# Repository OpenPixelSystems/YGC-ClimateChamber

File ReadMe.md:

# Climate Chamber Control System - Technical Documentation

A Flask-based climate chamber control system for Raspberry Pi providing precise temperature control using Peltier elements, real-time monitoring, and flow-based control sequences.

## Overview

This technical documentation is intended for developers and system administrators who need to understand the architecture, modify the system, or add new hardware components.

**For Users**: See `USER_GUIDE.md` for connection instructions and `INTERFACE_MANUAL.md` for application usage.

**Key Technologies:**
- Flask 3.1.1 web framework with Jinja2 templates
- RPi.GPIO for hardware control
- Adafruit CircuitPython libraries for sensors
- SQLite for data logging
- Chart.js for real-time visualization
- PID-based temperature control

---

## Architecture

### Frontend

The frontend is a Flask-rendered web application using HTML templates, JavaScript, and CSS.

**Location:** `app/frontend/`

**Technologies:**
- **Flask Templates (Jinja2)**: Server-side HTML rendering
- **JavaScript**: Client-side interactivity and real-time updates
- **CSS**: Custom styling with responsive design
- **AJAX**: Asynchronous communication with backend APIs

**Key Pages:**
- `home.html` - Main dashboard with quick temperature input
- `setupGraph.html` - Temperature profile creation interface
- `displayGraph.html` - Real-time graph display during active cycles
- `manualControl.html` - Manual hardware control interface
- `flow_designer.html` - Visual flow-based control designer
- `configEditor.html` - System configuration editor
- `databaseViewer.html` - Historical data viewer
- `logs_viewer.html` - System logs browser
- `wifi_networks.html` - WiFi network configuration

**Frontend Features:**
- Real-time temperature plotting using Chart.js or similar
- Drag-and-drop flow designer for creating temperature sequences
- Responsive forms for configuration editing
- Live status updates via periodic AJAX polling
- Flash messages for user feedback

---

### Backend

The backend follows a modular, interface-driven architecture with clear separation of concerns.

**Location:** `app/backend/`

**Technologies:**
- **Flask 3.1.1**: Web framework and API routing
- **RPi.GPIO**: Raspberry Pi GPIO control for hardware interfacing
- **Adafruit CircuitPython Libraries**:
  - `adafruit-circuitpython-mpl3115a2` - Pressure/temperature sensor
  - `adafruit-circuitpython-ads1x15` - Analog-to-Digital converter
- **SQLite**: Local database for data logging (`database.db`)
- **Python 3.x**: Core programming language

**Architecture Layers:**

#### 1. **Interfaces** (`app/backend/Interfaces/`)
Define contracts for all major components:
- `ISensor.py` - Sensor reading interface
- `IDriver.py` - Hardware driver interface
- `IClimateChamber.py` - Climate control interface
- `IConfigManager.py` - Configuration management
- `IDatabaseManager.py` - Database operations
- And more...

#### 2. **Implementations** (`app/backend/Implementations/`)
Concrete implementations of interfaces:
- `ClimateChamber.py` - Main climate control logic with PID control
- `ClimateChamberController.py` - High-level controller orchestration
- `SensorReader.py` - Reads all configured sensors
- `ConfigManager.py` - Loads and validates JSON configurations
- `DatabaseManager.py` - SQLite operations for logging and retrieval
- `FanController.py` - Fan speed control
- `RelayController.py` - Relay switching (e.g., for fridge control)

#### 3. **Drivers** (`app/backend/Drivers/`)
Low-level hardware drivers for motor controllers:
- `BTS7960Driver.py` - High-power motor driver for Peltier modules (up to 43A)
- `TB6612FNGDriver.py` - Dual motor driver for smaller Peltier/fan modules

#### 4. **Sensors** (`app/backend/Sensors/`)
Sensor implementations:
- `NTCTemperatureSensor.py` - NTC thermistor reading via ADC
- `DS18B20.py` - Digital temperature sensor (1-Wire)
- `DS18B20Cluster.py` - Multiple DS18B20 sensors
- `MPL3115A2.py` - I2C pressure and temperature sensor
- `ADS1115.py` - 16-bit ADC for analog sensors

#### 5. **Modules** (`app/backend/Modules/`)
Higher-level hardware abstractions:
- `PeltierModule.py` - Peltier element control (heating/cooling)
- `FanModule.py` - Fan control with PWM speed adjustment

#### 6. **Services** (`app/backend/Services/`)
Business logic and orchestration:
- `GuardingService.py` - Safety monitoring and emergency stops
- `TemperatuurService.py` - Temperature validation and processing
- `CalculationService.py` - PID calculations and control algorithms

#### 7. **Configuration** (`app/backend/config/`)
JSON-based configuration files:
- `raspberry_pi_config.json` - Hardware pin mappings and sensor definitions
- `control_config.json` - PID parameters and control settings
- `graph_config.json` - Stored temperature profiles

#### 8. **Flow Execution** (`app/backend/FlowExecution/`)
- `FlowExecutor.py` - Executes visual flow-based temperature sequences

#### 9. **Application State** (`app/backend/app_state.py`)
Singleton pattern for managing global application state:
- Initializes all components via factory methods
- Provides shared access to services and controllers
- Handles system reload and restart operations

---

## How It Works

### 1. **Temperature Control Loop**

The system uses a PID (Proportional-Integral-Derivative) control loop:

1. **Sensor Reading**: `SensorReader` polls all configured temperature sensors
2. **Calculation**: `CalculationService` compares current vs. desired temperature and calculates PID output
3. **Hardware Control**: Based on PID output:
   - **Positive output** → Heat mode: Peltier modules heat, fridge relay OFF
   - **Negative output** → Cool mode: Peltier modules cool or fridge relay ON
4. **Safety Monitoring**: `GuardingService` continuously checks sensor limits
5. **Logging**: `DatabaseManager` records all data points to SQLite database

### 2. **Peltier Module Control**

Peltier elements are thermoelectric devices that can heat or cool based on current direction:

- **Heating**: Current flows one direction (RPWM active, LPWM off)
- **Cooling**: Current flows opposite direction (LPWM active, RPWM off)
- **PWM Duty Cycle**: Controls heating/cooling intensity (0-100%)
- **Driver Selection**: System supports BTS7960 (high power) or TB6612FNG (lower power)

### 3. **Web Interface Communication**

1. User creates temperature profile via web interface
2. Frontend sends AJAX request to Flask route
3. Route handler validates input and calls backend service
4. Backend starts control loop and begins logging
5. Frontend polls for updates and renders real-time graphs

### 4. **Configuration System**

All hardware is defined in `raspberry_pi_config.json`:
```json
{
  "Temperature_inside_top": {
    "type": "NTC",
    "editable": {
      "SDA": 2,
      "SCL": 3,
      "read_pin": 0,
      "i2c_address": "0x4A",
      "beta_coefficient": 3600.0
    }
  },
  "Peltier_240W": {
    "type": "peltier",
    "editable": {
      "driver_type": "BTS7960",
      "RPWM": 13,
      "LPWM": 19,
      "R_EN": 5,
      "L_EN": 6,
      "PWM_FREQUENCY": 5000,
      "Duty cycle limit": 100
    }
  }
}
```

---

## Hardware Configuration

### Supported Hardware Components

#### **Temperature Sensors**
- **NTC Thermistors**: Via ADS1115 16-bit ADC
- **DS18B20**: Digital 1-Wire temperature sensors
- **MPL3115A2**: I2C pressure and temperature sensor

#### **Peltier Drivers**
- **BTS7960**: High-current (up to 43A) dual H-bridge for large Peltier modules
- **TB6612FNG**: Dual DC motor driver for smaller modules

#### **Other Components**
- **Fans**: PWM-controlled cooling fans
- **Relays**: For controlling external devices (e.g., refrigerator)

---

## Adapting to Different Hardware

### Adding a New Sensor

1. **Create sensor class** in `app/backend/Sensors/`:
```python
from app.backend.Interfaces.ISensor import ISensor

class MySensor(ISensor):
    def __init__(self, config):
        self.config = config

    def read(self):
        # Your sensor reading logic
        return temperature_value
```

2. **Add to SensorReader** in `app/backend/Implementations/SensorReader.py`:
```python
elif sensor_config.type == "MySensor":
    from app.backend.Sensors.MySensor import MySensor
    sensor = MySensor(sensor_config)
```

3. **Update configuration** in `raspberry_pi_config.json`:
```json
{
  "My_Temperature_Sensor": {
    "name": "My_Temperature_Sensor",
    "type": "MySensor",
    "editable": {
      "gpio_pin": 17,
      "custom_parameter": 123
    },
    "unit": "degrees"
  }
}
```

### Adding a New Motor Driver

1. **Create driver class** in `app/backend/Drivers/`:
```python
from app.backend.Interfaces.IDriver import IDriver

class MyDriver(IDriver):
    def __init__(self, config):
        # Initialize GPIO pins
        pass

    def heat(self, duty_cycle):
        # Implement heating logic
        pass

    def cool(self, duty_cycle):
        # Implement cooling logic
        pass

    def stop(self):
        # Stop all outputs
        pass
```

2. **Add to PeltierModule** in `app/backend/Modules/PeltierModule.py`:
```python
class DriverType(Enum):
    TB6612FNG = "TB6612FNG"
    BTS7960 = "BTS7960"
    MY_DRIVER = "MY_DRIVER"  # Add your driver

# In __init__:
if self.driver_type == DriverType.MY_DRIVER.value:
    from app.backend.Drivers.MyDriver import MyDriver
    self.driver = MyDriver(config)
```

3. **Update configuration**:
```json
{
  "Peltier_Custom": {
    "type": "peltier",
    "editable": {
      "driver_type": "MY_DRIVER",
      "pin1": 13,
      "pin2": 19,
      "pwm_frequency": 5000
    }
  }
}
```

### Changing GPIO Pin Assignments

Edit `app/backend/config/raspberry_pi_config.json` to change pin numbers:
```json
{
  "Peltier_240W": {
    "editable": {
      "RPWM": 13,  // Change to your pin number
      "LPWM": 19,  // Change to your pin number
      "R_EN": 5,
      "L_EN": 6
    }
  }
}
```

**Important**: After changing GPIO pins, restart the service:
```bash
sudo systemctl restart climatechamber.service
```

---

## Development Setup

### Local Development

1. Clone repository and create virtual environment:
```bash
git clone https://gitlab.com/tmc-climatechamber/climatechamber.git
cd climatechamber
python -m venv .venv
source .venv/bin/activate  # On Windows: .venv\Scripts\activate
pip install -r requirements.txt
```

2. Run development server:
```bash
python run.py
```

3. Access at `http://localhost:5000`

### Raspberry Pi Deployment

The system is pre-configured to run as a systemd service on Raspberry Pi. For fresh installations:

1. Clone repository on Raspberry Pi
2. Run setup script: `./setup_rp4.sh`
3. Service starts automatically on boot

---

## Project Structure

```
climatechamber/
├── app/
│   ├── __init__.py                 # Flask app factory
│   ├── backend/
│   │   ├── app_state.py            # Singleton application state
│   │   ├── Dataclasses/            # Data models and configurations
│   │   ├── Drivers/                # Low-level hardware drivers
│   │   ├── Sensors/                # Sensor implementations
│   │   ├── Modules/                # Hardware module abstractions
│   │   ├── Implementations/        # Core business logic
│   │   ├── Interfaces/             # Abstract interfaces
│   │   ├── Services/               # Business services
│   │   ├── FlowExecution/          # Flow-based control
│   │   ├── Providers/              # GPIO and hardware providers
│   │   ├── Technical/              # Logging and utilities
│   │   └── config/                 # JSON configuration files
│   ├── frontend/
│   │   ├── static/                 # CSS, JS, fonts
│   │   └── templates/              # HTML templates
│   └── routes/                     # Flask route handlers
├── run.py                          # Application entry point
├── requirements.txt                # Python dependencies
├── database.db                     # SQLite database
├── setup_rp4.sh                    # Raspberry Pi setup script
└── README.md                       # This file
```

---

## API Routes

| Route | Method | Description |
|-------|--------|-------------|
| `/` | GET | Home page with quick temperature input |
| `/status` | GET | Health check endpoint |
| `/submit-temperature` | POST | Start constant temperature cycle |
| `/manual-control` | GET | Manual hardware control interface |
| `/setup-graph` | GET/POST | Create temperature profiles |
| `/display-graph` | GET | Real-time monitoring |
| `/flow-designer` | GET/POST | Visual flow designer |
| `/database-viewer` | GET | View historical data |
| `/config-editor` | GET/POST | Edit system configuration |
| `/logs` | GET | View system logs |
| `/wifi` | GET/POST | Manage WiFi connections |

---

## Configuration Files

### raspberry_pi_config.json
Defines all hardware components and GPIO pin mappings.

### control_config.json
Contains PID tuning parameters and control loop settings.

### graph_config.json
Stores saved temperature profiles.

---

## Safety Features

1. **Temperature Limits**: Configurable min/max values per sensor
2. **Safety-Critical Sensors**: Emergency stops if limits exceeded
3. **Guarding Service**: Continuous monitoring of all sensors
4. **Emergency Stop**: Immediate hardware shutdown capability
5. **Duty Cycle Limits**: Prevents over-driving Peltier elements
6. **Cycle Locking**: Prevents starting multiple cycles simultaneously

---

## Development

### Adding New Features

The system follows the **Interface-Implementation pattern**:
1. Define interface in `Interfaces/`
2. Create implementation in `Implementations/`
3. Register in `app_state.py` factory methods
4. Add route handler in `routes/`
5. Create frontend template if needed

### Testing

Unit tests are located in `unittest/` directory.

---

## Common Development Issues

### GPIO Permission Errors
```bash
sudo usermod -a -G gpio $USER
# Log out and back in for changes to take effect
```

### I2C Not Enabled
```bash
sudo raspi-config
# Interface Options → I2C → Enable
```

### Service Debugging
```bash
# View real-time logs
sudo journalctl -u climatechamber.service -f

# Check service status
sudo systemctl status climatechamber.service

# Restart service
sudo systemctl restart climatechamber.service
```

### Python Import Errors
Ensure virtual environment is activated and all dependencies are installed:
```bash
source .venv/bin/activate
pip install -r requirements.txt
```

---

## Contributing

When adding new features:
1. Follow the Interface-Implementation pattern
2. Add corresponding route handlers in `app/routes/`
3. Update frontend templates as needed
4. Document changes in code comments
5. Test thoroughly before committing

---

## License

[Add your license information here]

## Support

For technical issues, check the logs and review this documentation. For user-facing questions, direct users to `USER_GUIDE.md` and `INTERFACE_MANUAL.md`.

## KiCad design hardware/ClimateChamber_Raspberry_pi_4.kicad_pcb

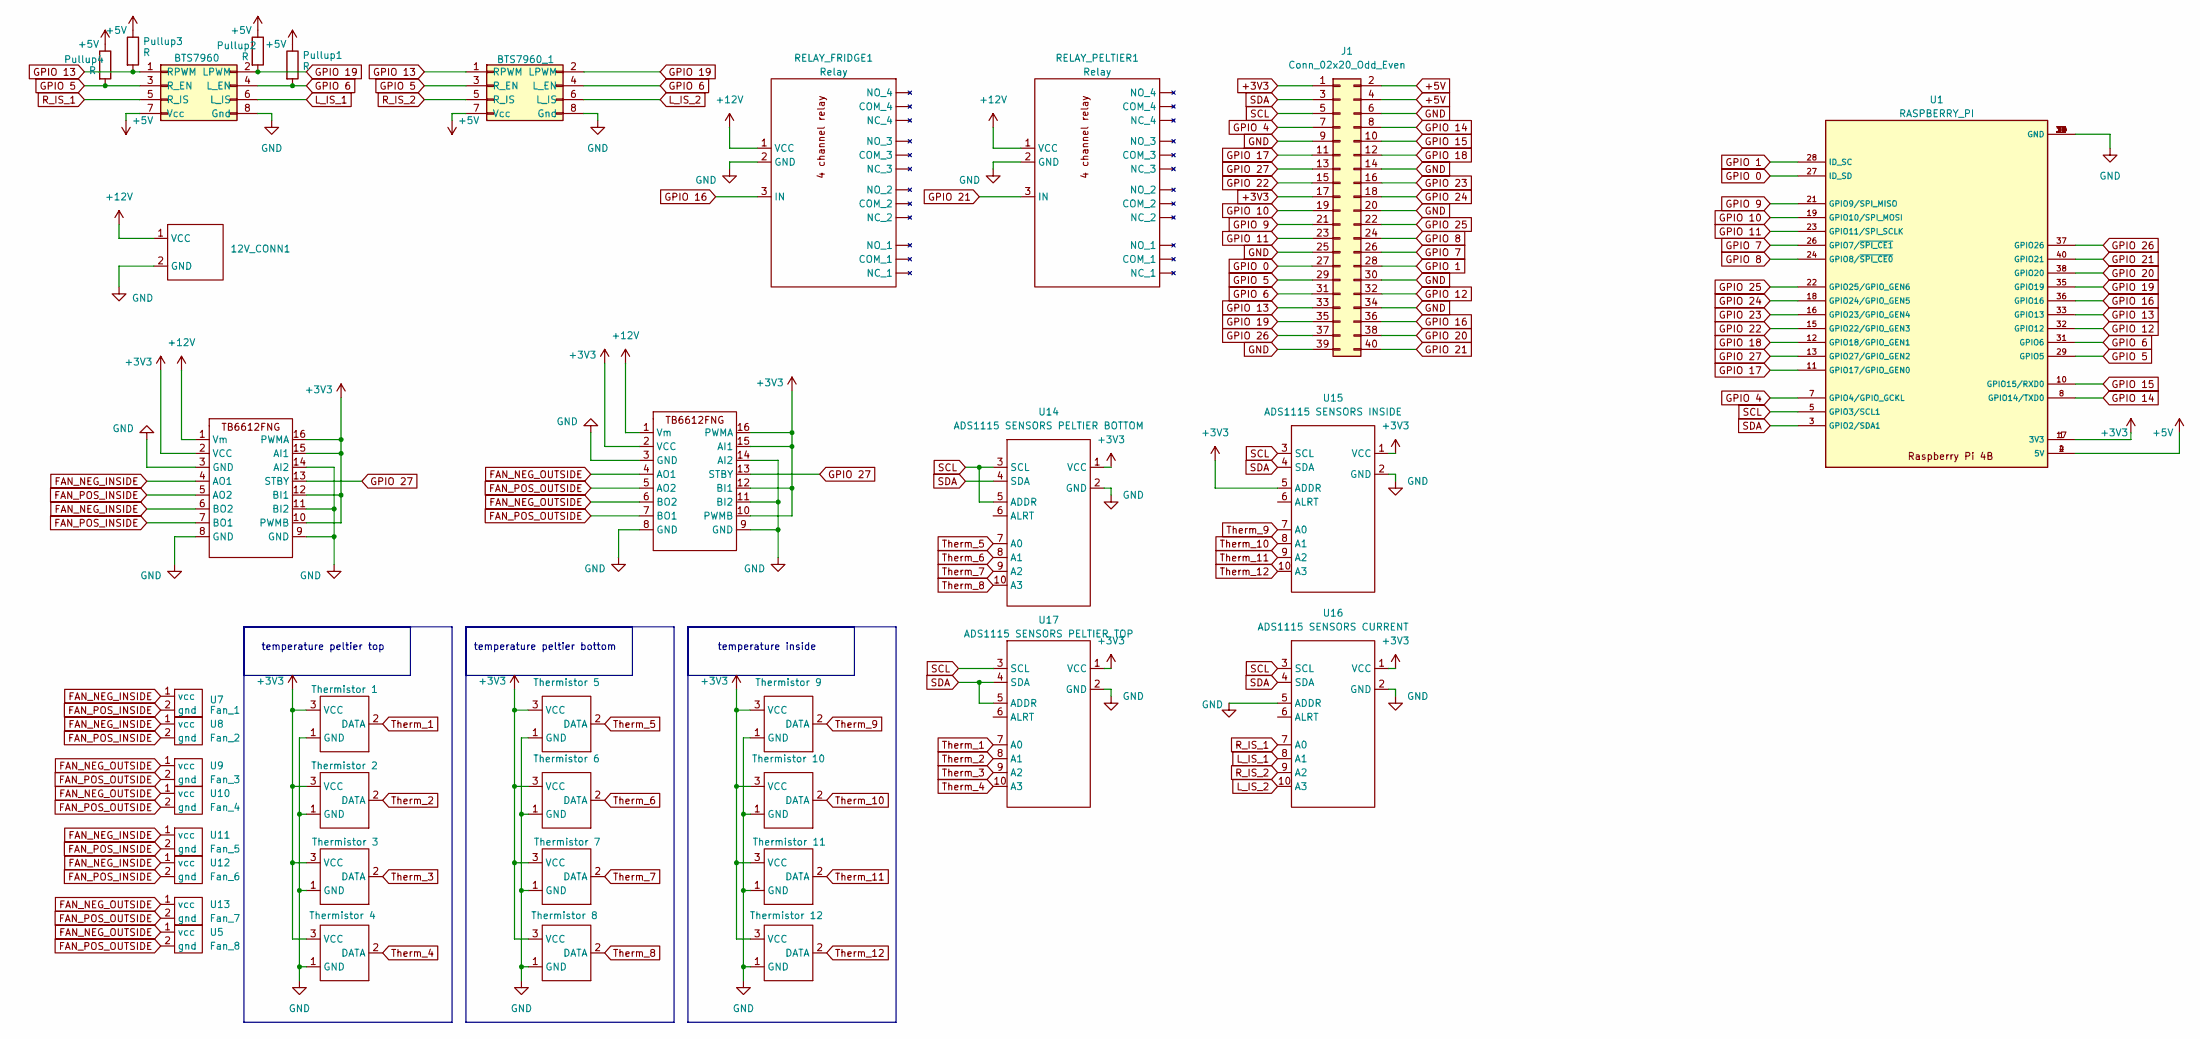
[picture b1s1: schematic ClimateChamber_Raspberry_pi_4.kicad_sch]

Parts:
12V_CONN1: 12V_CONN
BTS7960_1: BTS7960
BTS7960_2: BTS7960
FAN_DRIVER_1: Fan driver 2; TB6612FNG
FAN_DRIVER_2: Fan driver 1; TB6612FNG
J1: Conn_02x20_Odd_Even; PinHeader_2x20_P2.54mm_Vertical
Pullup1, Pullup2, Pullup3, Pullup4: R; R_1206_3216Metric_Pad1.30x1.75mm_HandSolder
RELAY_FRIDGE1: Relay; 4 channel relay
RELAY_PELTIER1: Relay; 4 channel relay
Therm1: Thermistor 1; Thermistor
Therm2: Thermistor 2; Thermistor
Therm3: Thermistor 3; Thermistor
Therm4: Thermistor 4; Thermistor
Therm5: Thermistor 5; Thermistor
Therm6: Thermistor 6; Thermistor
Therm7: Thermistor 7; Thermistor
Therm8: Thermistor 8; Thermistor
Therm9: Thermistor 9; Thermistor
Therm10: Thermistor 10; Thermistor
Therm11: Thermistor 11; Thermistor
Therm12: Thermistor 12; Thermistor
U1: RASPBERRY_PI; MODULE_RASPBERRY_PI_4B_4GB_pinout
U5: Fan_8; Fan_header
U7: Fan_1; Fan_header
U8: Fan_2; Fan_header
U9: Fan_3; Fan_header
U10: Fan_4; Fan_header
U11: Fan_5; Fan_header
U12: Fan_6; Fan_header
U13: Fan_7; Fan_header
U14: ADS1115 SENSORS PELTIER BOTTOM; ADS1115
U15: ADS1115 SENSORS INSIDE; ADS1115
U16: ADS1115 SENSORS CURRENT; ADS1115
U17: ADS1115 SENSORS PELTIER TOP; ADS1115

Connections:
+3V3: FAN_DRIVER_1.2 (VCC), FAN_DRIVER_1.10 (PWMB), FAN_DRIVER_1.12 (BI1), FAN_DRIVER_1.15 (AI1), FAN_DRIVER_1.16 (PWMA), FAN_DRIVER_2.2 (VCC), FAN_DRIVER_2.10 (PWMB), FAN_DRIVER_2.12 (BI1), FAN_DRIVER_2.15 (AI1), FAN_DRIVER_2.16 (PWMA), J1.1, J1.17, Therm1.3 (VCC), Therm2.3 (VCC), Therm3.3 (VCC), Therm4.3 (VCC), Therm5.3 (VCC), Therm6.3 (VCC), Therm7.3 (VCC), Therm8.3 (VCC), Therm9.3 (VCC), Therm10.3 (VCC), Therm11.3 (VCC), Therm12.3 (VCC), U1.1 (3V3), U1.17 (3V3), U14.1 (VCC), U15.1 (VCC), U15.5 (ADDR), U16.1 (VCC), U17.1 (VCC)
+5V: BTS7960_1.7 (Vcc), BTS7960_2.7 (Vcc), J1.2, J1.4, Pullup1.1, Pullup2.1, Pullup3.1, Pullup4.1, U1.2 (5V), U1.4 (5V)
+12V: 12V_CONN1.1 (VCC), FAN_DRIVER_1.1 (Vm), FAN_DRIVER_2.1 (Vm), RELAY_FRIDGE1.1 (VCC), RELAY_PELTIER1.1 (VCC)
FAN_NEG_INSIDE: FAN_DRIVER_1.4 (AO1), FAN_DRIVER_1.6 (BO2), U7.1 (vcc), U8.1 (vcc), U11.1 (vcc), U12.1 (vcc)
FAN_NEG_OUTSIDE: FAN_DRIVER_2.4 (AO1), FAN_DRIVER_2.6 (BO2), U5.1 (vcc), U9.1 (vcc), U10.1 (vcc), U13.1 (vcc)
FAN_POS_INSIDE: FAN_DRIVER_1.5 (AO2), FAN_DRIVER_1.7 (BO1), U7.2 (gnd), U8.2 (gnd), U11.2 (gnd), U12.2 (gnd)
FAN_POS_OUTSIDE: FAN_DRIVER_2.5 (AO2), FAN_DRIVER_2.7 (BO1), U5.2 (gnd), U9.2 (gnd), U10.2 (gnd), U13.2 (gnd)
GND: 12V_CONN1.2 (GND), BTS7960_1.8 (Gnd), BTS7960_2.8 (Gnd), FAN_DRIVER_1.3 (GND), FAN_DRIVER_1.8 (GND), FAN_DRIVER_1.9 (GND), FAN_DRIVER_1.11 (BI2), FAN_DRIVER_1.14 (AI2), FAN_DRIVER_2.3 (GND), FAN_DRIVER_2.8 (GND), FAN_DRIVER_2.9 (GND), FAN_DRIVER_2.11 (BI2), FAN_DRIVER_2.14 (AI2), J1.6, J1.9, J1.14, J1.20, J1.25, J1.30, J1.34, J1.39, RELAY_FRIDGE1.2 (GND), RELAY_PELTIER1.2 (GND), Therm1.1 (GND), Therm2.1 (GND), Therm3.1 (GND), Therm4.1 (GND), Therm5.1 (GND), Therm6.1 (GND), Therm7.1 (GND), Therm8.1 (GND), Therm9.1 (GND), Therm10.1 (GND), Therm11.1 (GND), Therm12.1 (GND), U1.6 (GND), U1.9 (GND), U1.14 (GND), U1.20 (GND), U1.25 (GND), U1.30 (GND), U1.34 (GND), U1.39 (GND), U14.2 (GND), U15.2 (GND), U16.2 (GND), U16.5 (ADDR), U17.2 (GND)
GPIO 0: J1.27, U1.27 (ID_SD)
GPIO 1: J1.28, U1.28 (ID_SC)
GPIO 4: J1.7, U1.7 (GPIO4/GPIO_GCKL)
GPIO 5: BTS7960_1.3 (R_EN), BTS7960_2.3 (R_EN), J1.29, Pullup4.2, U1.29 (GPIO5)
GPIO 6: BTS7960_1.4 (L_EN), BTS7960_2.4 (L_EN), J1.31, Pullup1.2, U1.31 (GPIO6)
GPIO 7: J1.26, U1.26 (GPIO7/~SPI_CE1)
GPIO 8: J1.24, U1.24 (GPIO8/~SPI_CE0)
GPIO 9: J1.21, U1.21 (GPIO9/SPI_MISO)
GPIO 10: J1.19, U1.19 (GPIO10/SPI_MOSI)
GPIO 11: J1.23, U1.23 (GPIO11/SPI_SCLK)
GPIO 12: J1.32, U1.32 (GPIO12)
GPIO 13: BTS7960_1.1 (RPWM), BTS7960_2.1 (RPWM), J1.33, Pullup3.2, U1.33 (GPIO13)
GPIO 14: J1.8, U1.8 (GPIO14/TXD0)
GPIO 15: J1.10, U1.10 (GPIO15/RXD0)
GPIO 16: J1.36, RELAY_FRIDGE1.3 (IN), U1.36 (GPIO16)
GPIO 17: J1.11, U1.11 (GPIO17/GPIO_GEN0)
GPIO 18: J1.12, U1.12 (GPIO18/GPIO_GEN1)
GPIO 19: BTS7960_1.2 (LPWM), BTS7960_2.2 (LPWM), J1.35, Pullup2.2, U1.35 (GPIO19)
GPIO 20: J1.38, U1.38 (GPIO20)
GPIO 21: J1.40, RELAY_PELTIER1.3 (IN), U1.40 (GPIO21)
GPIO 22: J1.15, U1.15 (GPIO22/GPIO_GEN3)
GPIO 23: J1.16, U1.16 (GPIO23/GPIO_GEN4)
GPIO 24: J1.18, U1.18 (GPIO24/GPIO_GEN5)
GPIO 25: J1.22, U1.22 (GPIO25/GPIO_GEN6)
GPIO 26: J1.37, U1.37 (GPIO26)
GPIO 27: FAN_DRIVER_1.13 (STBY), FAN_DRIVER_2.13 (STBY), J1.13, U1.13 (GPIO27/GPIO_GEN2)
L_IS_1: BTS7960_2.6 (L_IS), U16.8 (A1)
L_IS_2: BTS7960_1.6 (L_IS), U16.10 (A3)
R_IS_1: BTS7960_2.5 (R_IS), U16.7 (A0)
R_IS_2: BTS7960_1.5 (R_IS), U16.9 (A2)
SCL: J1.5, U1.5 (GPIO3/SCL1), U14.3 (SCL), U14.5 (ADDR), U15.3 (SCL), U16.3 (SCL), U17.3 (SCL)
SDA: J1.3, U1.3 (GPIO2/SDA1), U14.4 (SDA), U15.4 (SDA), U16.4 (SDA), U17.4 (SDA), U17.5 (ADDR)
Therm_1: Therm1.2 (DATA), U17.7 (A0)
Therm_2: Therm2.2 (DATA), U17.8 (A1)
Therm_3: Therm3.2 (DATA), U17.9 (A2)
Therm_4: Therm4.2 (DATA), U17.10 (A3)
Therm_5: Therm5.2 (DATA), U14.7 (A0)
Therm_6: Therm6.2 (DATA), U14.8 (A1)
Therm_7: Therm7.2 (DATA), U14.9 (A2)
Therm_8: Therm8.2 (DATA), U14.10 (A3)
Therm_9: Therm9.2 (DATA), U15.7 (A0)
Therm_10: Therm10.2 (DATA), U15.8 (A1)
Therm_11: Therm11.2 (DATA), U15.9 (A2)
Therm_12: Therm12.2 (DATA), U15.10 (A3)

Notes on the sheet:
temperature peltier bottom
temperature inside
temperature peltier top

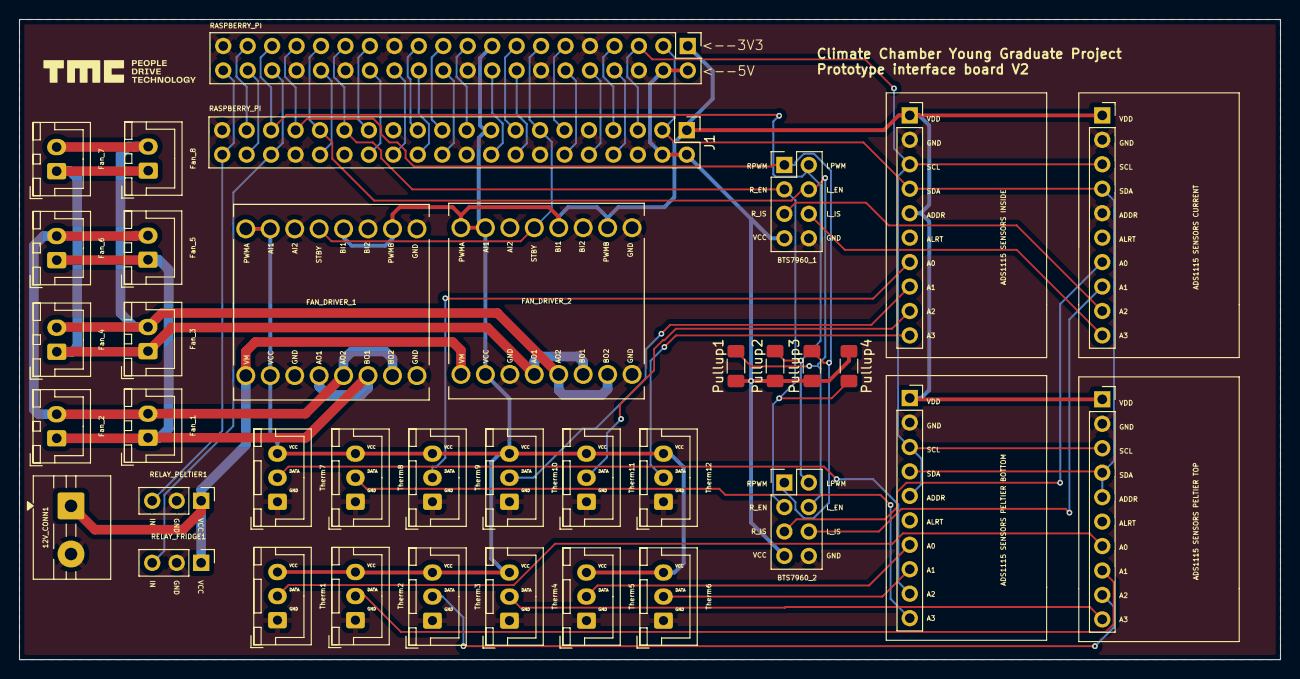
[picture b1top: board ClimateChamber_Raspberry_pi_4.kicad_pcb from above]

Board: 2 copper layers, 131.0 x 66.5 mm, 37 parts (0 on the bottom side), 52 nets.

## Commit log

2025-04-16 Add projects files to repo
2025-04-16 Update .gitlab-ci.yml file
2025-04-16 Edit readme file
2025-04-18 Edit readme file and implement dockerfile for easy deployment
2025-04-22 add database page
2025-04-23 populate database viewer chart based on selected run
2025-04-24 Remove status icon from database viewer screen
2025-04-24 Add option to delete selected cycle from database
2025-04-24 edit gitlab-ci file
2025-04-25 edit readme and rename app to climateChamberInterface
2025-04-25 remove database from project
2025-04-25 add db files to gitignore and update readme file
2025-04-25 add config blueprint and move logic from main
2025-04-25 add other config files to editor
2025-04-28 Fix config for raspberry_pi_config.json Fix database viewer full screen
2025-05-03 Resolve "Backend: streamline readings sensors and controlling peltier modules"
2025-05-03 Add other config files to config manager and reload info if config is edited
2025-05-03 add pycallgraph to visualise call structure
2025-05-04 change app_state singleton creation
2025-05-04 add TODO to ConfigManager.py
2025-05-19 Solve tightly coupled code
2025-05-21 rework sensor reading logic
2025-05-24 remove sensors from sensor file
2025-05-24 update adafruit import
2025-05-24 place sensor reading in infinite thread
2025-05-24 refine dht22 sensor reading
2025-05-24 remove dht22 add peltier pid steering logic qdd current sensor reqding
2025-05-24 implement manual steering
2025-05-24 implement manual control and log calculation values visualise calculation values add delete all button
2025-05-25 Fix database logging for multiple sensors Fix database viewer Split sensor reading into categories
2025-05-26 add MPL3115A2 reading functionality
2025-05-26 add MPL3115A2 reading to database logging
2025-05-28 enable raspi AP mode
2025-05-29 add temperature guarding to peltier steering finetune calculation protocol implementing adaptive steering
2025-05-30 add logging functionality add guarding functionality
2025-05-30 Fix copy by reference to copy by value
2025-05-30 Edit logging and fix manual steering
2025-05-31 Max duty cycle
2025-06-01 getrandomcolour()
2025-06-01 Tom v1
2025-06-06 Ras pi access point mode
2025-06-15 Apply 1 suggestion(s) to 1 file(s)
2025-06-21 Resolve issue sensor reading with DS18B20
2025-06-23 exclude claude.md
2025-06-23 claude run1
2025-06-23 rework css files to fix layout inconsistency
2025-06-23 refactor chart manager
2025-06-23 add min max annotation to setup graph
2025-06-23 add temperature values to sensor list when cycle is active
2025-06-23 rework control layout
2025-06-23 implement export data
2025-06-23 implement import data
2025-06-25 remove vertical line from visualisation
2025-06-25 implement data zooming
2025-06-25 minor fix
2025-06-25 add restart
2025-06-25 add storage visualiser
2025-06-26 fix restart response
2025-07-22 make sensor reading threaded
2025-07-22 make setup graph chart dynamicaly scaling
2025-07-23 edit settings button
2025-08-01 edit manual control slider send mechanism
2025-08-01 edit background reading
2025-08-01 show sensor value origin info
2025-08-01 show sensor value origin info extra
2025-08-01 add other current readers
2025-08-01 make chart js accessible offline
    (cherry picked from commit 2f528a63c051269546d3e1508bce63795968e31a)
2025-08-02 add test for ads motor driver combo
2025-08-02 add git force pull
2025-08-02 add voltage offset to ads sensor
2025-08-02 fix offset values
2025-08-02 add logging webpage and edit sensor reading origin
2025-08-02 add guardianservice notification when exceeding threshold
2025-08-02 move notif
2025-08-02 disable current sensors when peltier is disabled
2025-08-02 add ads1115 calibration test
2025-08-02 edit cali test
2025-08-02 edit cali test2
2025-08-02 edit cali test3
2025-08-02 add calibration to config
2025-08-02 set rp dual wifi
2025-08-02 set rp dual wifi extended
2025-08-02 cleanup
2025-08-02 add delete logs button
2025-08-02 restart service if config edited
2025-08-02 edit sens
2025-08-02 rework guardianservice
2025-08-13 add ntc sensor implementation to system
2025-08-13 add ntc sensor implementation to databaselogging
2025-08-15 add test script for tnc sensor
2025-08-15 add logging
2025-08-15 convert hex to int
2025-08-15 edit address
2025-08-15 change viable sensor
2025-08-17 utilise average of temp sensors inside climate chamber for steering
2025-08-17 add average to setup page
2025-08-17 edit setup-graph logic
2025-08-18 remove current sense component until fixed
2025-08-18 edit displaygraph ux
2025-08-19 add raspi ip addr to homepage
2025-08-21 add wifi setup page
2025-08-21 add wifi setup page2
2025-08-21 add wifi setup page3
2025-08-21 visualise connection
2025-08-23 add continuous cycle through webpages
2025-08-23 fix merge
2025-08-23 add raspberry pi connectivity and repository setup files
2025-08-24 add raspberry pi systemd and kiosk mode setup files
2025-08-24 manager wifi connection
2025-08-24 make fontsaawesome available offline
2025-08-24 fix viable sensors missing
2025-09-21 add relay controller to system
2025-09-21 edit i2c address
2025-09-22 change coordinate handling
2025-09-22 remove animation
2025-09-22 remove start and end options
2025-09-22 add flow execution logic
2025-09-22 solve double logging issue
2025-09-22 remove some excess debug and stop once end node is reached
2025-09-22 temp exclude
2025-09-22 add long run test
2025-09-22 add max_rico_heating
2025-09-23 add other sensors
2025-09-23 add other sensors pt2
2025-09-24 edit pid controller
2025-09-24 edit designer
2025-09-24 edit flow execution
2025-09-25 enable driver when flow starts
2025-09-28 edit config
2025-09-29 optimise performance frontend
2025-10-02 add documentation, readme, user guide and interface manual
2025-10-09 fix: fixed issue where temperature flow got stuck in a state
2025-10-10 feat: app possibility to get/set temperature on the fly
2025-10-10 style: formatting with Black
2026-01-05 feat: add hardware schematics
